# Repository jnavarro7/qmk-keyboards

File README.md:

# qmk-keyboards
 qmk keyboards

## Keyboards
Right hand 4x2 keypad:

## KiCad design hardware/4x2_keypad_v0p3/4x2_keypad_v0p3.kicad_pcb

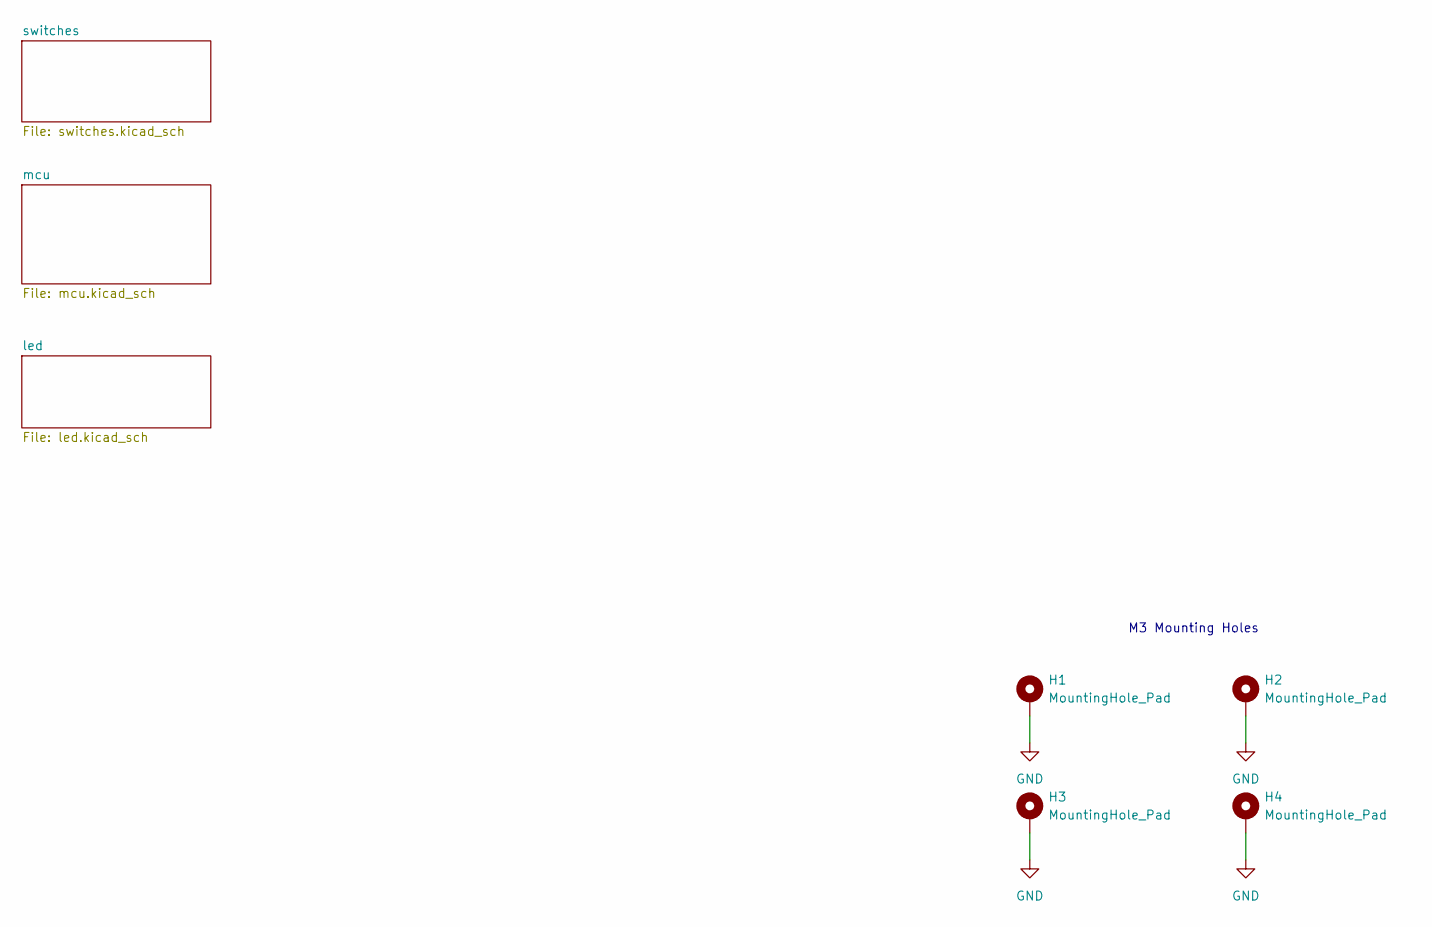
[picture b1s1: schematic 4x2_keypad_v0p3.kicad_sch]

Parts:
H1, H2, H3, H4: MountingHole_Pad; MountingHole_3.2mm_M3_ISO7380_Pad_TopOnly

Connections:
GND: H1.1 (1_1), H2.1 (1_1), H3.1 (1_1), H4.1 (1_1); also elsewhere on the board

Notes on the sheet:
M3 Mounting Holes

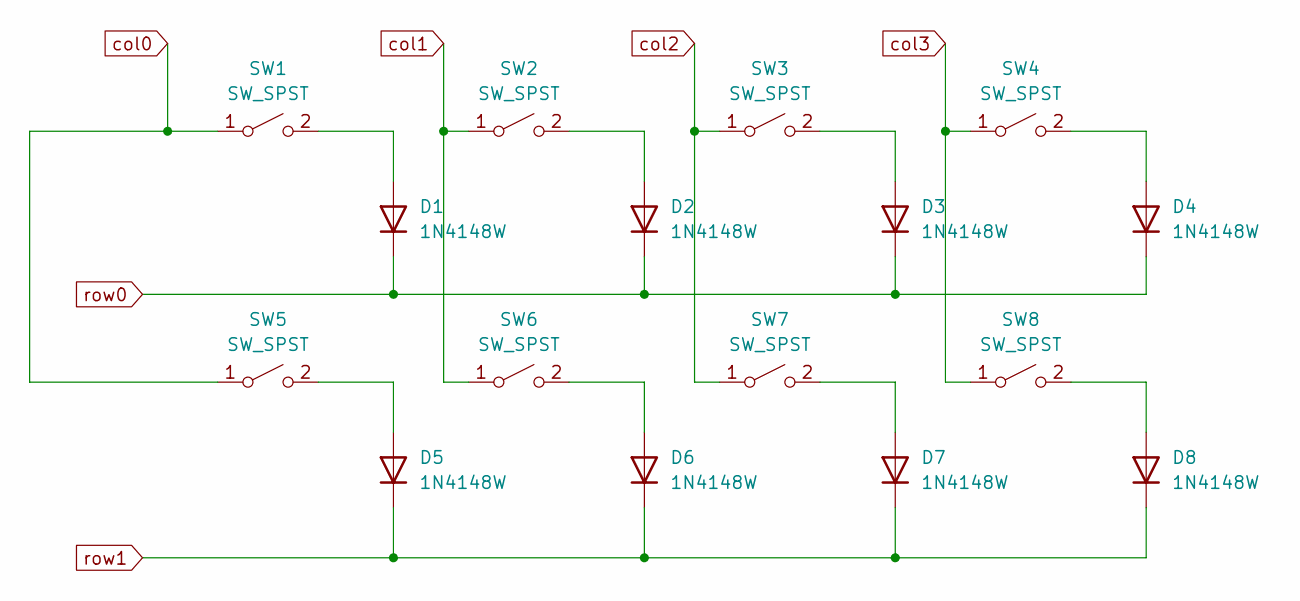
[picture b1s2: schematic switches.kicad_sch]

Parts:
D1, D2, D3, D4, D5, D6, D7, D8: 1N4148W; D_SOD-123
SW1, SW2, SW3, SW4, SW5, SW6, SW7, SW8: SW_SPST; SW_Cherry_MX_1.00u_Plate

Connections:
unnamed: D1.2 (A), SW1.2 (B)
unnamed: D2.2 (A), SW2.2 (B)
unnamed: D3.2 (A), SW3.2 (B)
unnamed: D4.2 (A), SW4.2 (B)
unnamed: D5.2 (A), SW5.2 (B)
unnamed: D6.2 (A), SW6.2 (B)
unnamed: D7.2 (A), SW7.2 (B)
unnamed: D8.2 (A), SW8.2 (B)
col0: SW1.1 (A), SW5.1 (A); also elsewhere on the board
col1: SW2.1 (A), SW6.1 (A); also elsewhere on the board
col2: SW3.1 (A), SW7.1 (A); also elsewhere on the board
col3: SW4.1 (A), SW8.1 (A); also elsewhere on the board
row0: D1.1 (K), D2.1 (K), D3.1 (K), D4.1 (K); also elsewhere on the board
row1: D5.1 (K), D6.1 (K), D7.1 (K), D8.1 (K); also elsewhere on the board

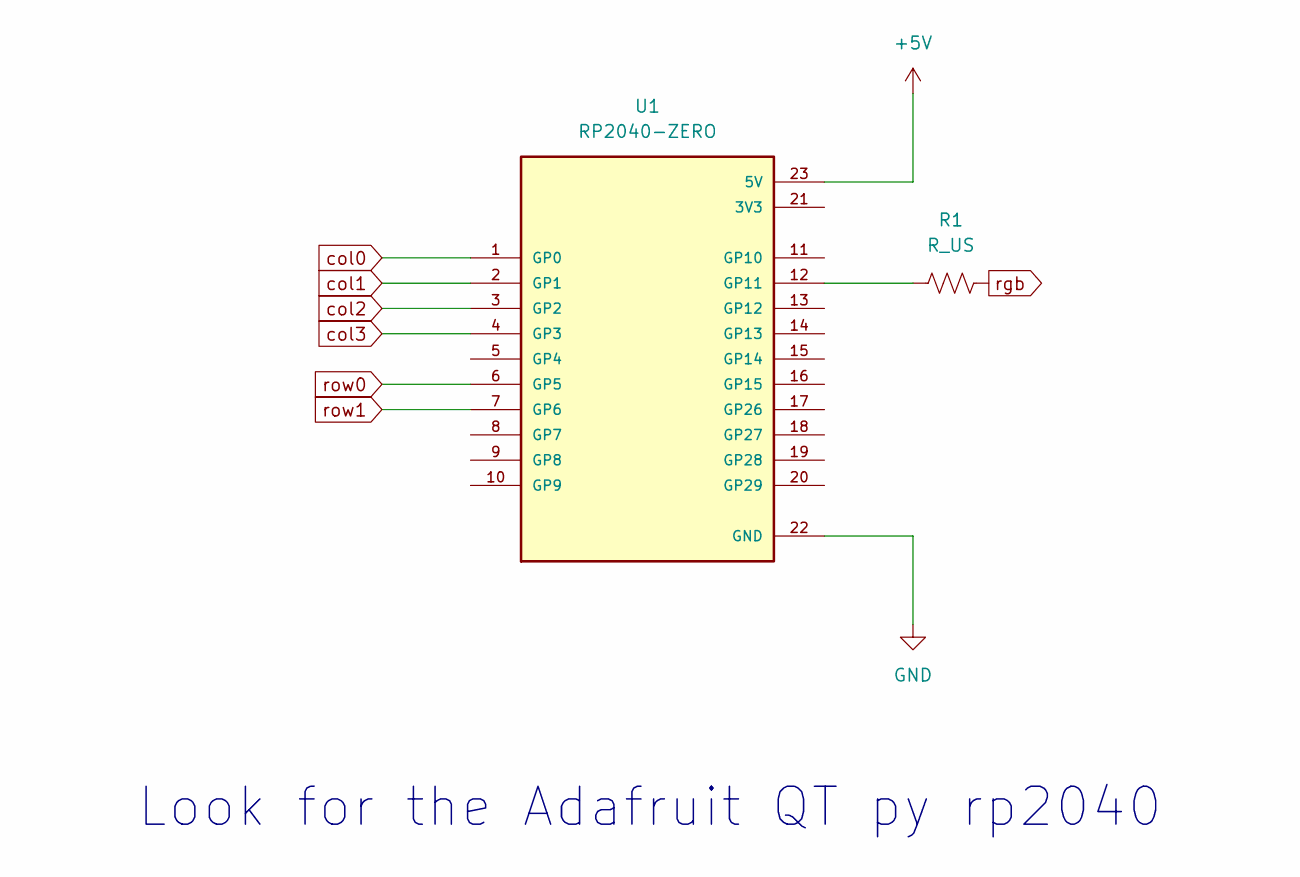
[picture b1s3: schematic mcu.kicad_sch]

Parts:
R1: R_US; R_0805_2012Metric_Pad1.20x1.40mm_HandSolder
U1: RP2040-ZERO; MODULE_RP2040-ZERO; PARTREV NA

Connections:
+5V: U1.23 (5V); also elsewhere on the board
GND: U1.22 (GND); also elsewhere on the board
unnamed: R1.1, U1.12 (GP11)
col0: U1.1 (GP0); also elsewhere on the board
col1: U1.2 (GP1); also elsewhere on the board
col2: U1.3 (GP2); also elsewhere on the board
col3: U1.4 (GP3); also elsewhere on the board
rgb: R1.2; also elsewhere on the board
row0: U1.6 (GP5); also elsewhere on the board
row1: U1.7 (GP6); also elsewhere on the board

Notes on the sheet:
Look for the Adafruit QT py rp2040

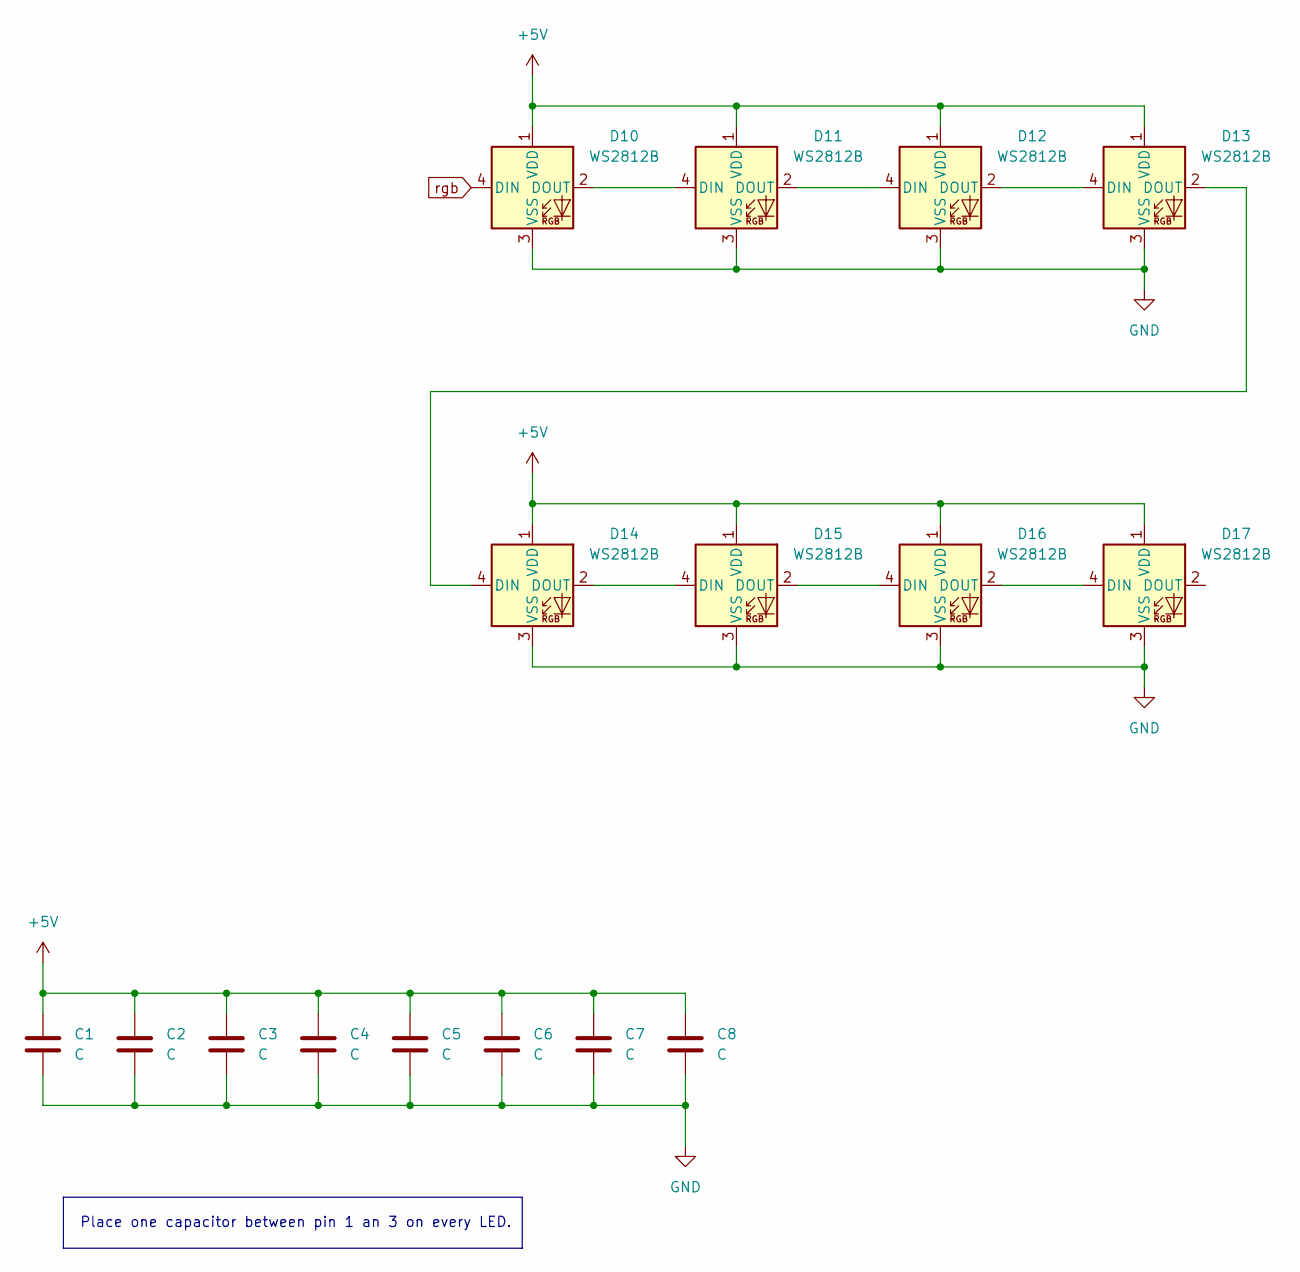
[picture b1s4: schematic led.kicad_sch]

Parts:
C1, C2, C3, C4, C5, C6, C7, C8: C; C_0805_2012Metric_Pad1.18x1.45mm_HandSolder
D10, D11, D12, D13, D14, D15, D16, D17: WS2812B; LED_WS2812B_PLCC4_5.0x5.0mm_P3.2mm

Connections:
+5V: C1.1, C2.1, C3.1, C4.1, C5.1, C6.1, C7.1, C8.1, D10.1 (VDD), D11.1 (VDD), D12.1 (VDD), D13.1 (VDD), D14.1 (VDD), D15.1 (VDD), D16.1 (VDD), D17.1 (VDD); also elsewhere on the board
GND: C1.2, C2.2, C3.2, C4.2, C5.2, C6.2, C7.2, C8.2, D10.3 (VSS), D11.3 (VSS), D12.3 (VSS), D13.3 (VSS), D14.3 (VSS), D15.3 (VSS), D16.3 (VSS), D17.3 (VSS); also elsewhere on the board
unnamed: D10.2 (DOUT), D11.4 (DIN)
unnamed: D11.2 (DOUT), D12.4 (DIN)
unnamed: D12.2 (DOUT), D13.4 (DIN)
unnamed: D13.2 (DOUT), D14.4 (DIN)
unnamed: D14.2 (DOUT), D15.4 (DIN)
unnamed: D15.2 (DOUT), D16.4 (DIN)
unnamed: D16.2 (DOUT), D17.4 (DIN)
rgb: D10.4 (DIN); also elsewhere on the board

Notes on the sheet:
Place one capacitor between pin 1 an 3 on every LED.

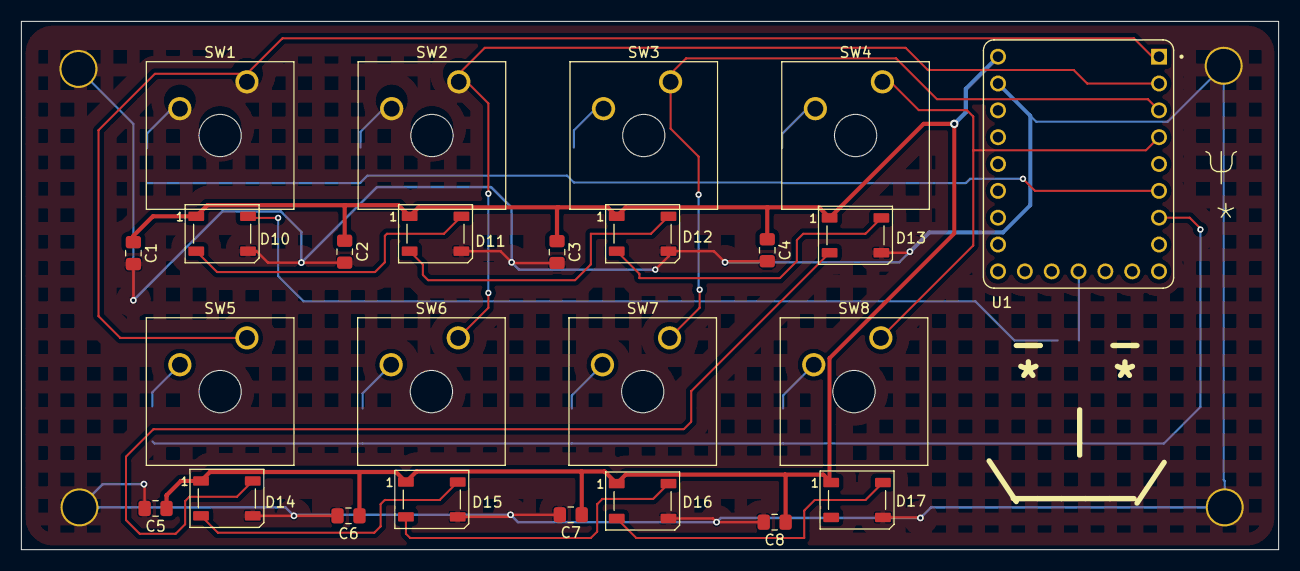
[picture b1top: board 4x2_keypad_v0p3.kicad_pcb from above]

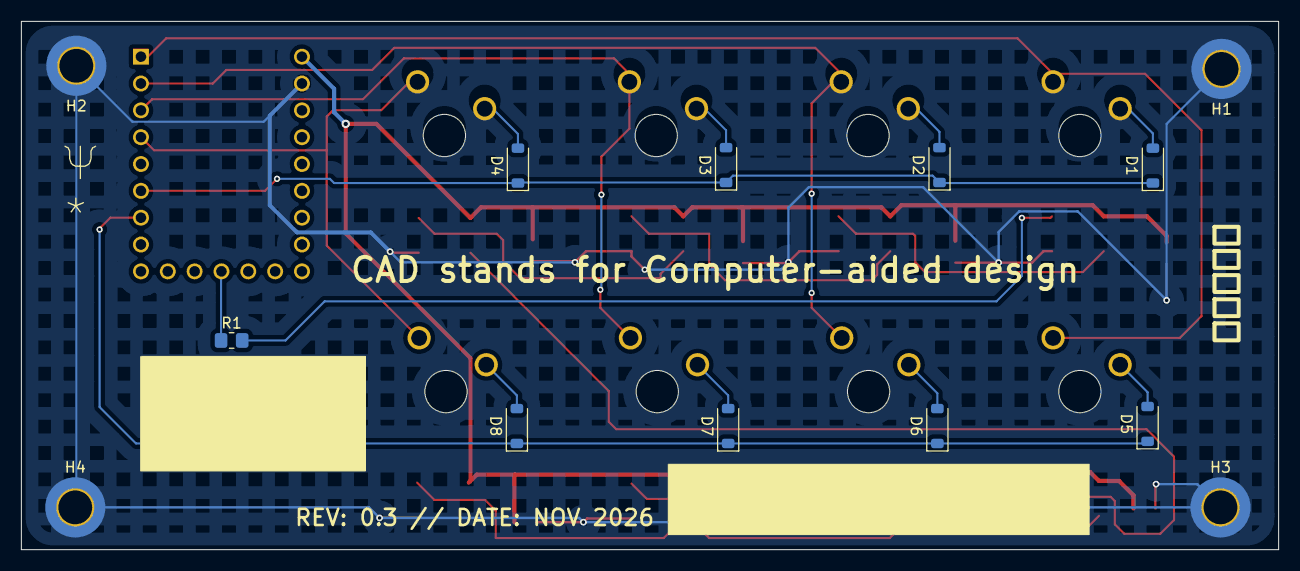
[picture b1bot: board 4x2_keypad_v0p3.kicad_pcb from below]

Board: 2 copper layers, 119.0 x 50.0 mm, 38 parts (13 on the bottom side), 25 nets.
